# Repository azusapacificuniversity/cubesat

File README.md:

# cubesat
This repository houses the design documents, files, code, etc in a multi-year project for [Azusa Pacific Univeristy](https://www.apu.edu/)'s department of [Engineering and Computer Science](https://www.apu.edu/clas/computerscience/) to design, fabricate, test, and have launched our very own nanosatellite!

A great primer on CubeSats is [NASA's CubeSat 101: Basic Concepts and Processes for First-Time CubeSat Developers (pdf)](https://www.nasa.gov/sites/default/files/atoms/files/nasa_csli_cubesat_101_508.pdf) from their page [https://www.nasa.gov/content/cubesat-launch-initiative-resources](https://www.nasa.gov/content/cubesat-launch-initiative-resources).

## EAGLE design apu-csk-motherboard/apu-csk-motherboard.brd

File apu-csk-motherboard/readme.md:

[Autodesk Eagle](https://www.autodesk.com/products/eagle/) Schematic, Board, and Library files for an APU-designed Open Source Hardware Pumpkin CubeSat
Kit-compatible Slot 0 Motherboard.  

This is a template, mechanically it should work, but electrically it doesn't really do much yet.  This is the
board outline and connectors for the main modules: a 104-pin CSK bus
with H1 and H2 connectors, an [iceWerx module](https://www.robotshop.com/en/devantech-icewerx-ice40-hx8k-fpga.html) with a Lattice iCE40HX8K
FPGA, and a Feather-compatible socket, which can take any number of
microcontroller boards such as the [SparkFun RISC-V RED-V Thing Plus](https://www.sparkfun.com/products/15799) or the
[Adafruit ESP32 Feather](https://www.adafruit.com/product/3405).  

This board is designed to work with the [Pumpkin Space](https://www.pumpkinspace.com/) - [CubeSat Kit Frame](http://cubesatkit.com/), for example parts:
```
710-00794       Base Plate Assembly
703-00289       Chassis Walls
710-00713       Large Aperture Cover Plate Assembly
```
from https://www.pumpkinspace.com/

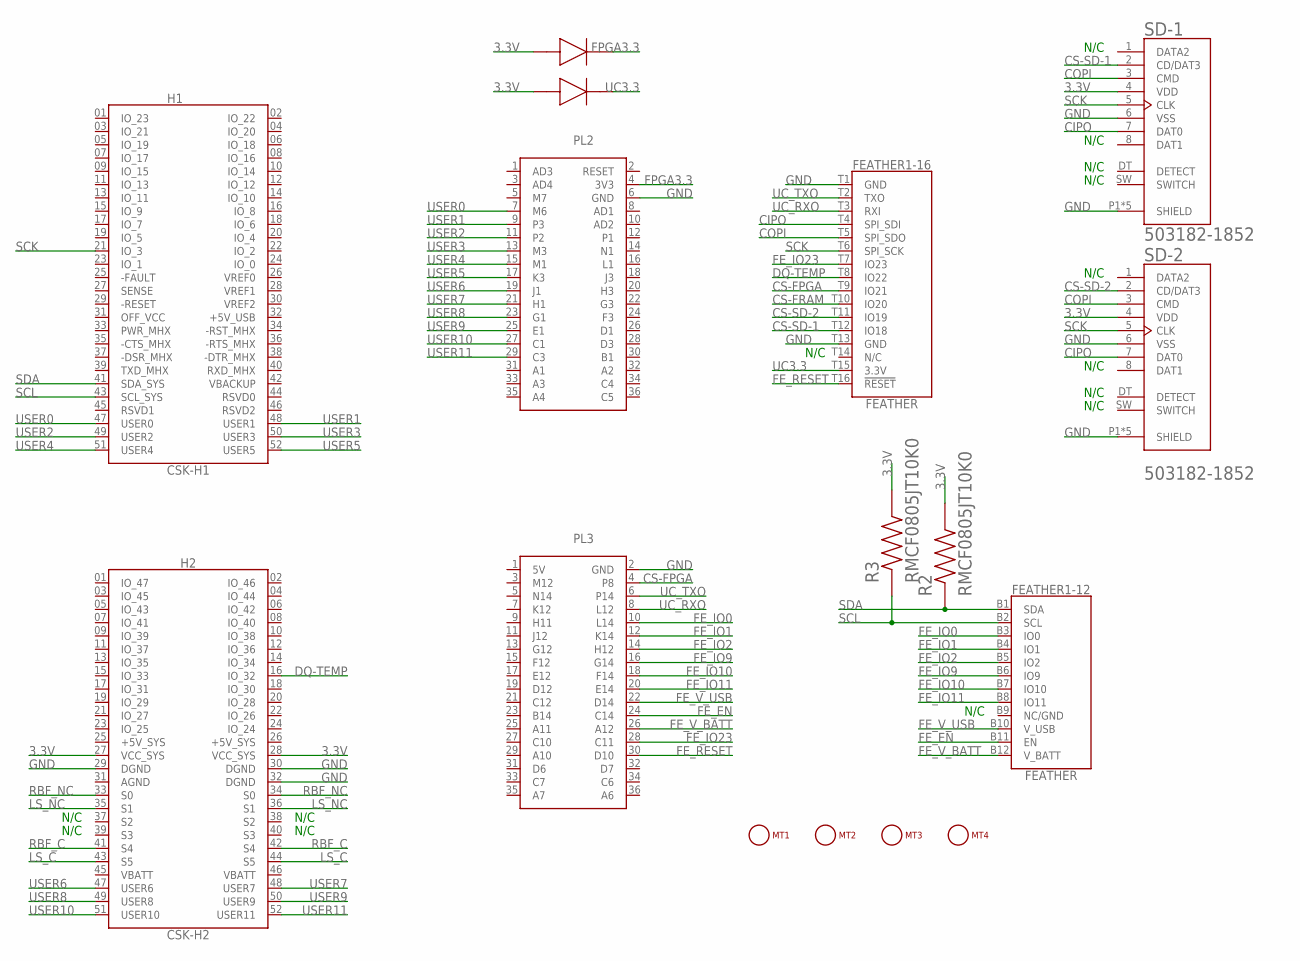
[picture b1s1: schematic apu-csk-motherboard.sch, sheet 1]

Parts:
B1, B2: DIO_PMEG4030ER,115
FEATHER1: FEATHER
H1: CSK-H1; SAMTEC_ESQ-126-37-G-D--NUMBERED-FOR-CUBESAT-BUS
H2: CSK-H2; SAMTEC_ESQ-126-37-G-D--NUMBERED-FOR-CUBESAT-BUS
MT1, MT2, MT3, MT4: MOUNTING_HOLE-125_250_ROUND; MT_125_250
PL2: ICEWERX-PL2; TE_4-1734506-1
PL3: ICEWERX-PL3; TE_4-1734506-1
R2, R3: RMCF0805JT10K0; RESC2012X65N
SD-1, SD-2: 503182-1852; MOLEX_503182-1852

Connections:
3.3V: B1.2 (ANODE), B2.2 (ANODE), H2.27 (VCC_SYS), H2.28 (VCC_SYS), R2.2, R3.2, SD-1.4 (VDD), SD-2.4 (VDD); also elsewhere on the board
CIPO: FEATHER1.T4 (SPI_SDI), SD-1.7 (DAT0), SD-2.7 (DAT0); also elsewhere on the board
COPI: FEATHER1.T5 (SPI_SDO), SD-1.3 (CMD), SD-2.3 (CMD); also elsewhere on the board
CS-FPGA: FEATHER1.T9 (IO21), PL3.4 (P8)
CS-FRAM: FEATHER1.T10 (IO20); also elsewhere on the board
CS-SD-1: FEATHER1.T12 (IO18), SD-1.2 (CD/DAT3)
CS-SD-2: FEATHER1.T11 (IO19), SD-2.2 (CD/DAT3)
DQ-TEMP: FEATHER1.T8 (IO22), H2.16 (IO_32); also elsewhere on the board
FE_EN: FEATHER1.B11 (EN), PL3.24 (C14)
FE_IO0: FEATHER1.B3 (IO0), PL3.10 (L14)
FE_IO1: FEATHER1.B4 (IO1), PL3.12 (K14)
FE_IO2: FEATHER1.B5 (IO2), PL3.14 (H12)
FE_IO9: FEATHER1.B6 (IO9), PL3.16 (G14)
FE_IO10: FEATHER1.B7 (IO10), PL3.18 (F14)
FE_IO11: FEATHER1.B8 (IO11), PL3.20 (E14)
FE_IO23: FEATHER1.T7 (IO23), PL3.28 (C11)
FE_RESET: FEATHER1.T16 (!RESET), PL3.30 (D10)
FE_V_BATT: FEATHER1.B12 (V_BATT), PL3.26 (A12)
FE_V_USB: FEATHER1.B10 (V_USB), PL3.22 (D14)
FPGA3.3: B1.1 (CATHODE), PL2.4 (3V3)
GND: FEATHER1.T1 (GND), FEATHER1.T13 (GND), H2.29 (DGND), H2.30 (DGND), H2.32 (DGND), PL2.6 (GND), PL3.2 (GND), SD-1.6 (VSS), SD-1.P1 (SHIELD), SD-1.P2 (SHIELD), SD-1.P3 (SHIELD), SD-1.P4 (SHIELD), SD-1.P5 (SHIELD), SD-2.6 (VSS), SD-2.P1 (SHIELD), SD-2.P2 (SHIELD), SD-2.P3 (SHIELD), SD-2.P4 (SHIELD), SD-2.P5 (SHIELD); also elsewhere on the board
LS_C: H2.43 (S5), H2.44 (S5); also elsewhere on the board
LS_NC: H2.35 (S1), H2.36 (S1); also elsewhere on the board
RBF_C: H2.41 (S4), H2.42 (S4); also elsewhere on the board
RBF_NC: H2.33 (S0), H2.34 (S0); also elsewhere on the board
SCK: FEATHER1.T6 (SPI_SCK), H1.21 (IO_3), SD-1.5 (CLK), SD-2.5 (CLK); also elsewhere on the board
SCL: FEATHER1.B2 (SCL), H1.43 (SCL_SYS), R3.1; also elsewhere on the board
SDA: FEATHER1.B1 (SDA), H1.41 (SDA_SYS), R2.1; also elsewhere on the board
UC3.3: B2.1 (CATHODE), FEATHER1.T15 (3.3V)
UC_RXO: FEATHER1.T3 (RXI), PL3.8 (L12)
UC_TXO: FEATHER1.T2 (TXO), PL3.6 (P14)
USER0: H1.47 (USER0), PL2.7 (M6)
USER1: H1.48 (USER1), PL2.9 (P3)
USER2: H1.49 (USER2), PL2.11 (P2)
USER3: H1.50 (USER3), PL2.13 (M3)
USER4: H1.51 (USER4), PL2.15 (M1)
USER5: H1.52 (USER5), PL2.17 (K3)
USER6: H2.47 (USER6), PL2.19 (J1)
USER7: H2.48 (USER7), PL2.21 (H1)
USER8: H2.49 (USER8), PL2.23 (G1)
USER9: H2.50 (USER9), PL2.25 (E1)
USER10: H2.51 (USER10), PL2.27 (C1)
USER11: H2.52 (USER11), PL2.29 (C3)

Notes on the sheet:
N/C

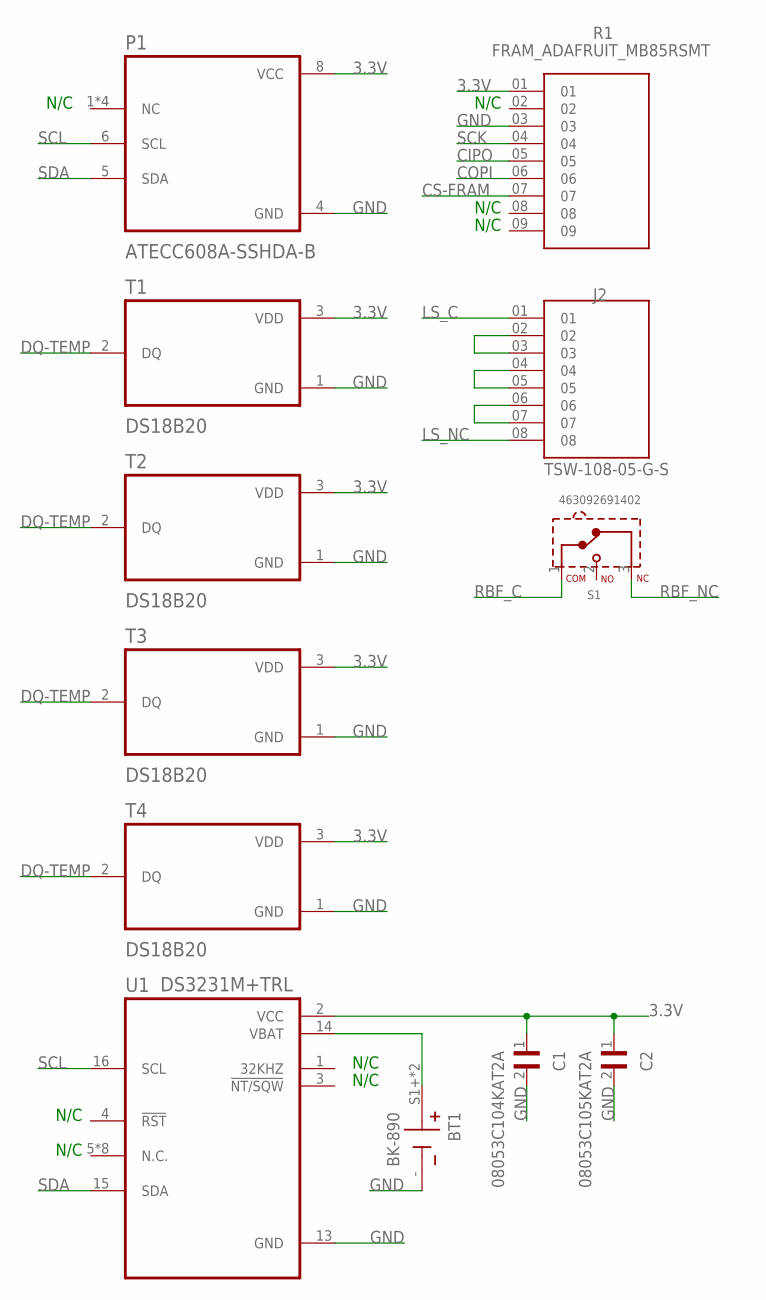
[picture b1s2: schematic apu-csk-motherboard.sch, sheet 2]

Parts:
BT1: BK-890; BAT_BK-890
C1: 08053C104KAT2A; CAPC2012X94N
C2: 08053C105KAT2A; CAPC2012X94N
J2: TSW-108-05-G-S; SAMTEC_TSW-108-05-G-S
P1: ATECC608A-SSHDA-B; SOIC127P600X175-8N
R1: FRAM_ADAFRUIT_MB85RSMT
S1: 463092691402
T1, T2, T3, T4: DS18B20; TO92269P495H695-3
U1: DS3231M+TRL; SOIC127P1032X265-16N

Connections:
3.3V: C1.1, C2.1, P1.8 (VCC), R1.01, T1.3 (VDD), T2.3 (VDD), T3.3 (VDD), T4.3 (VDD), U1.2 (VCC); also elsewhere on the board
CIPO: R1.05; also elsewhere on the board
COPI: R1.06; also elsewhere on the board
CS-FRAM: R1.07; also elsewhere on the board
DQ-TEMP: T1.2 (DQ), T2.2 (DQ), T3.2 (DQ), T4.2 (DQ); also elsewhere on the board
GND: BT1.-, C1.2, C2.2, P1.4 (GND), R1.03, T1.1 (GND), T2.1 (GND), T3.1 (GND), T4.1 (GND), U1.13 (GND); also elsewhere on the board
LS_C: J2.01; also elsewhere on the board
LS_NC: J2.08; also elsewhere on the board
unnamed: BT1.S1+ (+), BT1.S2+ (+), U1.14 (VBAT)
unnamed: J2.02, J2.03
unnamed: J2.04, J2.05
unnamed: J2.06, J2.07
RBF_C: S1.1 (COM); also elsewhere on the board
RBF_NC: S1.3 (NC); also elsewhere on the board
SCK: R1.04; also elsewhere on the board
SCL: P1.6 (SCL), U1.16 (SCL); also elsewhere on the board
SDA: P1.5 (SDA), U1.15 (SDA); also elsewhere on the board

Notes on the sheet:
N/C

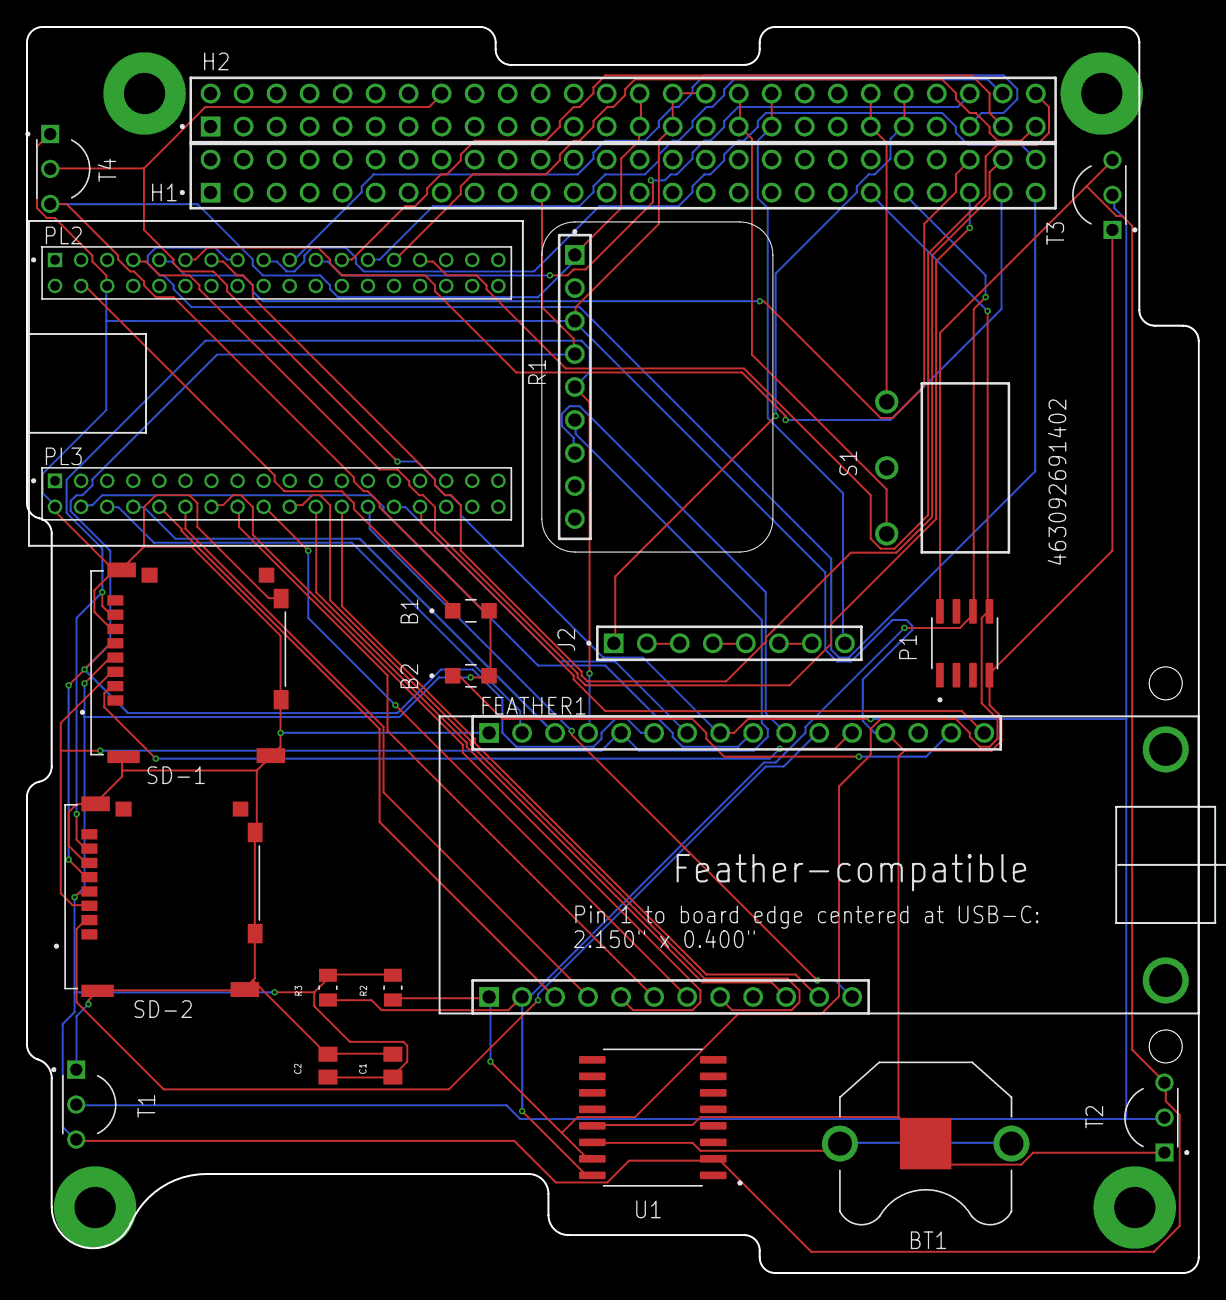
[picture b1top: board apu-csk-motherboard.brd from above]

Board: 2 copper layers, 90.2 x 95.9 mm, 27 parts (0 on the bottom side), 47 nets.

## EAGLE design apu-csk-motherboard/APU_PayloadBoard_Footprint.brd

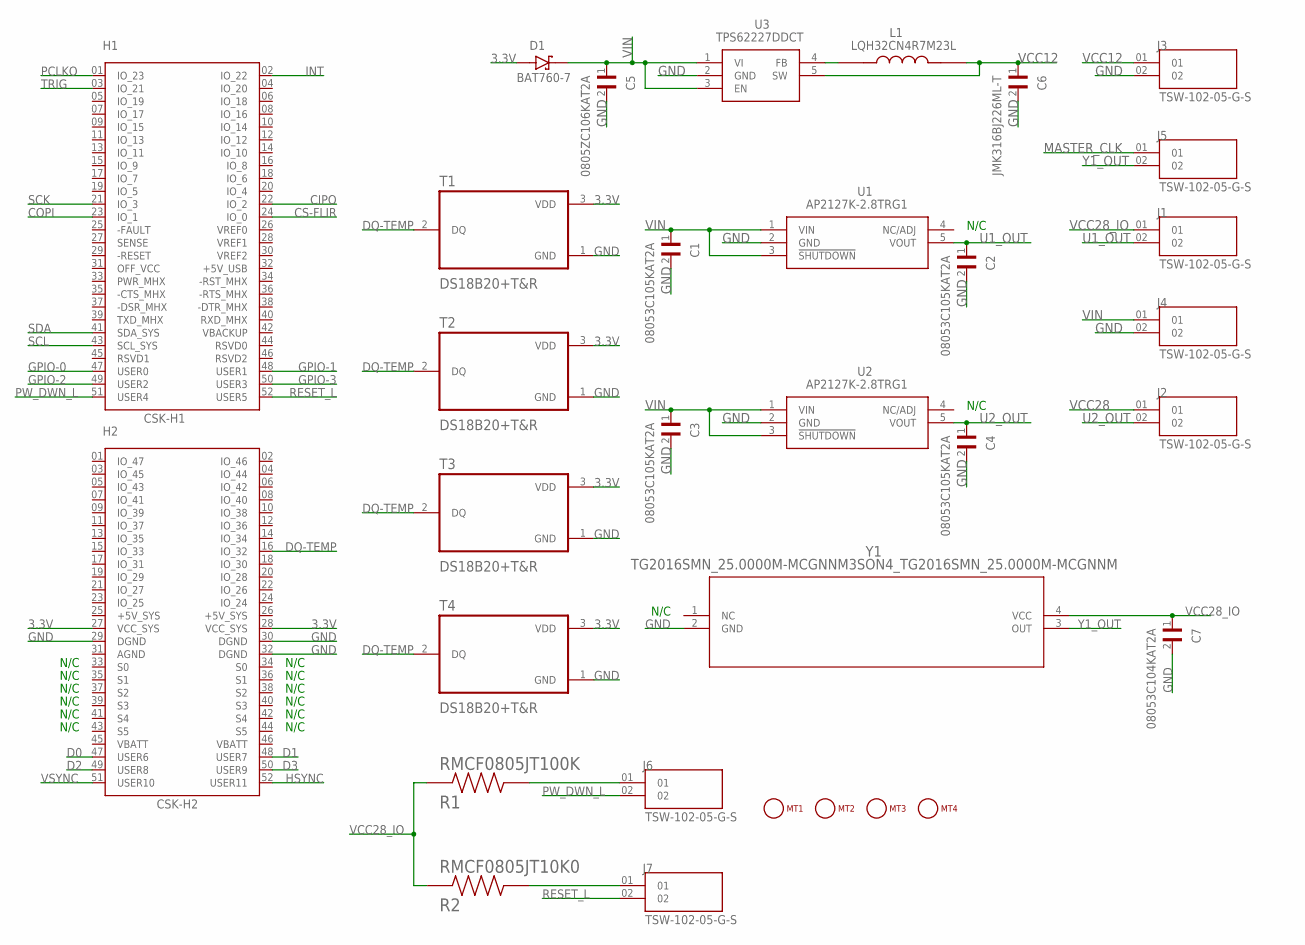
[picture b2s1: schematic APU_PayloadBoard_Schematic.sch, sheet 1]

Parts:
C1, C2, C3, C4: 08053C105KAT2A; CAPC2012X94N
C5: 0805ZC106KAT2A; CAPC2012X152N
C6: JMK316BJ226ML-T; CAPC3216X180N
C7: 08053C104KAT2A; CAPC2012X94N
D1: BAT760-7; SOD2513X120N
H1: CSK-H1; SAMTEC_ESQ-126-37-G-D--NUMBERED-FOR-CUBESAT-BUS
H2: CSK-H2; SAMTEC_ESQ-126-37-G-D--NUMBERED-FOR-CUBESAT-BUS
J1, J2, J3, J4, J5, J6, J7: TSW-102-05-G-S; SAMTEC_TSW-102-05-G-S
L1: LQH32CN4R7M23L; IND_LQH32CN4R7M23L
MT1, MT2, MT3, MT4: MOUNTING_HOLE-125_250_ROUND; MT_125_250
R1: RMCF0805JT100K; RESC2012X65N
R2: RMCF0805JT10K0; RESC2012X65N
T1, T2, T3, T4: DS18B20+T&R
U1, U2: AP2127K-2.8TRG1; SOT95P282X145-5N
U3: TPS62227DDCT; SOT95P280X110-5N
Y1: TG2016SMN_25.0000M-MCGNNM3SON4_TG2016SMN_25.0000M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; SON4_TG2016SMN_25.0000M-MCGNNM

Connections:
3.3V: D1.A, H2.27 (VCC_SYS), H2.28 (VCC_SYS), T1.3 (VDD), T2.3 (VDD), T3.3 (VDD), T4.3 (VDD); also elsewhere on the board
CIPO: H1.22 (IO_2); also elsewhere on the board
COPI: H1.23 (IO_1); also elsewhere on the board
CS-FLIR: H1.24 (IO_0); also elsewhere on the board
D0: H2.47 (USER6); also elsewhere on the board
D1: H2.48 (USER7); also elsewhere on the board
D2: H2.49 (USER8); also elsewhere on the board
D3: H2.50 (USER9); also elsewhere on the board
DQ-TEMP: H2.16 (IO_32), T1.2 (DQ), T2.2 (DQ), T3.2 (DQ), T4.2 (DQ)
GND: C1.2, C2.2, C3.2, C4.2, C5.2, C6.2, C7.2, H2.29 (DGND), H2.30 (DGND), H2.32 (DGND), J3.02, J4.02, T1.1 (GND), T2.1 (GND), T3.1 (GND), T4.1 (GND), U1.2 (GND), U2.2 (GND), U3.2 (GND), Y1.2 (GND); also elsewhere on the board
GPIO-0: H1.47 (USER0); also elsewhere on the board
GPIO-1: H1.48 (USER1); also elsewhere on the board
GPIO-2: H1.49 (USER2); also elsewhere on the board
GPIO-3: H1.50 (USER3); also elsewhere on the board
HSYNC: H2.52 (USER11); also elsewhere on the board
INT: H1.02 (IO_22); also elsewhere on the board
MASTER_CLK: J5.01; also elsewhere on the board
unnamed: L1.1, U3.4 (FB)
unnamed: J6.01, R1.2
unnamed: J7.01, R2.2
PCLKO: H1.01 (IO_23); also elsewhere on the board
PW_DWN_L: H1.51 (USER4), J6.02; also elsewhere on the board
RESET_L: H1.52 (USER5), J7.02; also elsewhere on the board
SCK: H1.21 (IO_3); also elsewhere on the board
SCL: H1.43 (SCL_SYS); also elsewhere on the board
SDA: H1.41 (SDA_SYS); also elsewhere on the board
TRIG: H1.03 (IO_21); also elsewhere on the board
U1_OUT: C2.1, J1.02, U1.5 (VOUT)
U2_OUT: C4.1, J2.02, U2.5 (VOUT)
VCC12: C6.1, J3.01, L1.2, U3.5 (SW); also elsewhere on the board
VCC28: J2.01; also elsewhere on the board
VCC28_IO: C7.1, J1.01, R1.1, R2.1, Y1.4 (VCC); also elsewhere on the board
VIN: C1.1, C3.1, C5.1, D1.C (K), J4.01, U1.1 (VIN), U1.3 (!SHUTDOWN), U2.1 (VIN), U2.3 (!SHUTDOWN), U3.1 (VI), U3.3 (EN)
VSYNC: H2.51 (USER10); also elsewhere on the board
Y1_OUT: J5.02, Y1.3 (OUT)

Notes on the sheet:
N/C

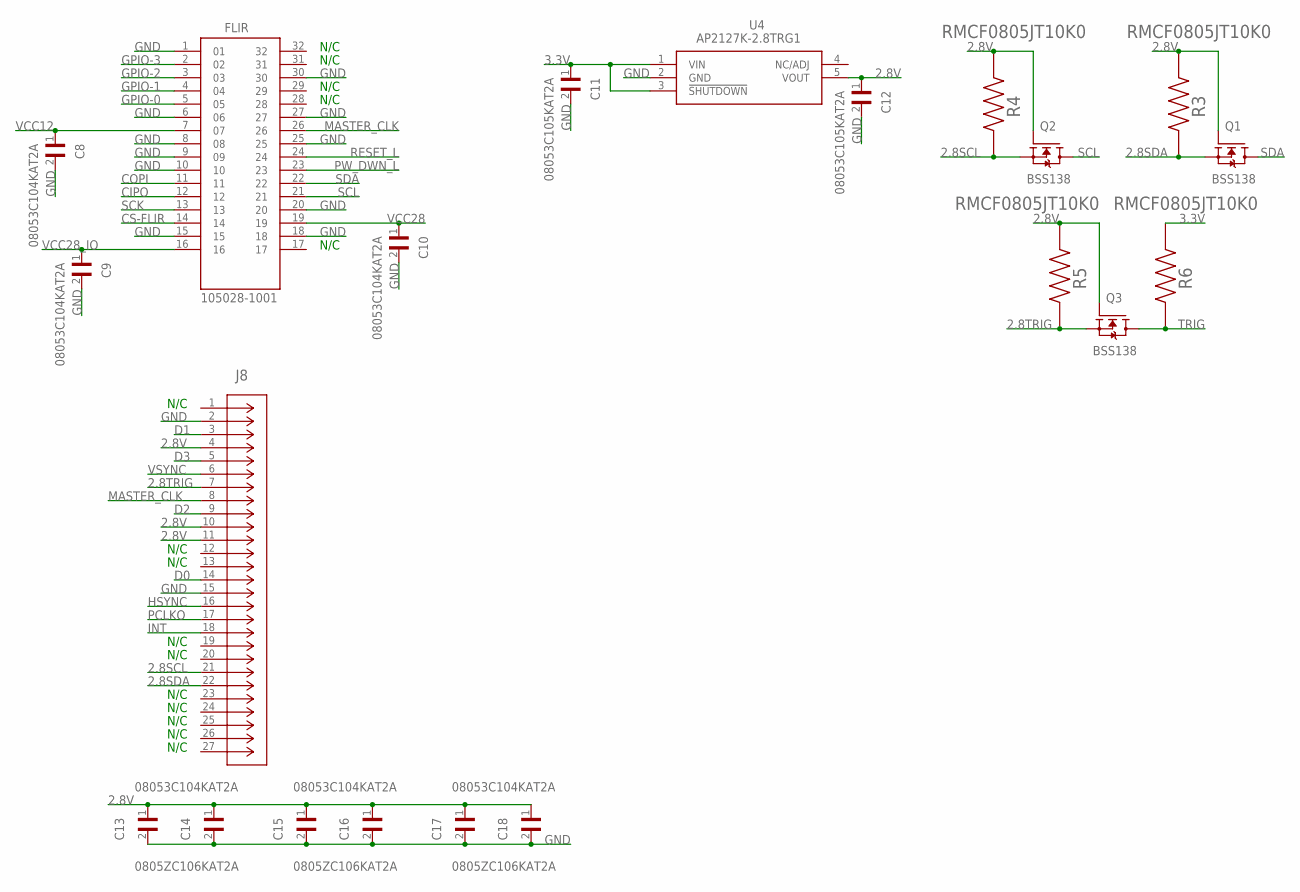
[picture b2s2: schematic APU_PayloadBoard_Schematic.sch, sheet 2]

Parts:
C8, C9, C10, C13, C15, C17: 08053C104KAT2A; CAPC2012X94N
C11, C12: 08053C105KAT2A; CAPC2012X94N
C14, C16, C18: 0805ZC106KAT2A; CAPC2012X152N
FLIR: 105028-1001; MOLEX_105028-1001
J8: SFV25R-1STE1LFCON25_1X25_DR_SFV_JAE; CON25_1X25_DR_SFV_JAE
Q1, Q2, Q3: BSS138; SOT95P240X111-3N
R3, R4, R5, R6: RMCF0805JT10K0; RESC2012X65N
U4: AP2127K-2.8TRG1; SOT95P282X145-5N

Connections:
2.8SCL: J8.21, Q2.2 (S), R4.1
2.8SDA: J8.22, Q1.2 (S), R3.1
2.8TRIG: J8.7, Q3.2 (S), R5.1
2.8V: C12.1, C13.1, C14.1, C15.1, C16.1, C17.1, C18.1, J8.4, J8.10, J8.11, Q1.1 (G), Q2.1 (G), Q3.1 (G), R3.2, R4.2, R5.2, U4.5 (VOUT)
3.3V: C11.1, R6.2, U4.1 (VIN), U4.3 (!SHUTDOWN); also elsewhere on the board
CIPO: FLIR.12; also elsewhere on the board
COPI: FLIR.11; also elsewhere on the board
CS-FLIR: FLIR.14; also elsewhere on the board
D0: J8.14; also elsewhere on the board
D1: J8.3; also elsewhere on the board
D2: J8.9; also elsewhere on the board
D3: J8.5; also elsewhere on the board
GND: C8.2, C9.2, C10.2, C11.2, C12.2, C13.2, C14.2, C15.2, C16.2, C17.2, C18.2, FLIR.1, FLIR.6, FLIR.8, FLIR.9, FLIR.10, FLIR.15, FLIR.18, FLIR.20, FLIR.25, FLIR.27, FLIR.30, J8.2, J8.15, U4.2 (GND); also elsewhere on the board
GPIO-0: FLIR.5; also elsewhere on the board
GPIO-1: FLIR.4; also elsewhere on the board
GPIO-2: FLIR.3; also elsewhere on the board
GPIO-3: FLIR.2; also elsewhere on the board
HSYNC: J8.16; also elsewhere on the board
INT: J8.18; also elsewhere on the board
MASTER_CLK: FLIR.26, J8.8; also elsewhere on the board
PCLKO: J8.17; also elsewhere on the board
PW_DWN_L: FLIR.23; also elsewhere on the board
RESET_L: FLIR.24; also elsewhere on the board
SCK: FLIR.13; also elsewhere on the board
SCL: FLIR.21, Q2.3 (D); also elsewhere on the board
SDA: FLIR.22, Q1.3 (D); also elsewhere on the board
TRIG: Q3.3 (D), R6.1; also elsewhere on the board
VCC12: C8.1, FLIR.7; also elsewhere on the board
VCC28: C10.1, FLIR.19; also elsewhere on the board
VCC28_IO: C9.1, FLIR.16; also elsewhere on the board
VSYNC: J8.6; also elsewhere on the board

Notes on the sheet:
N/C

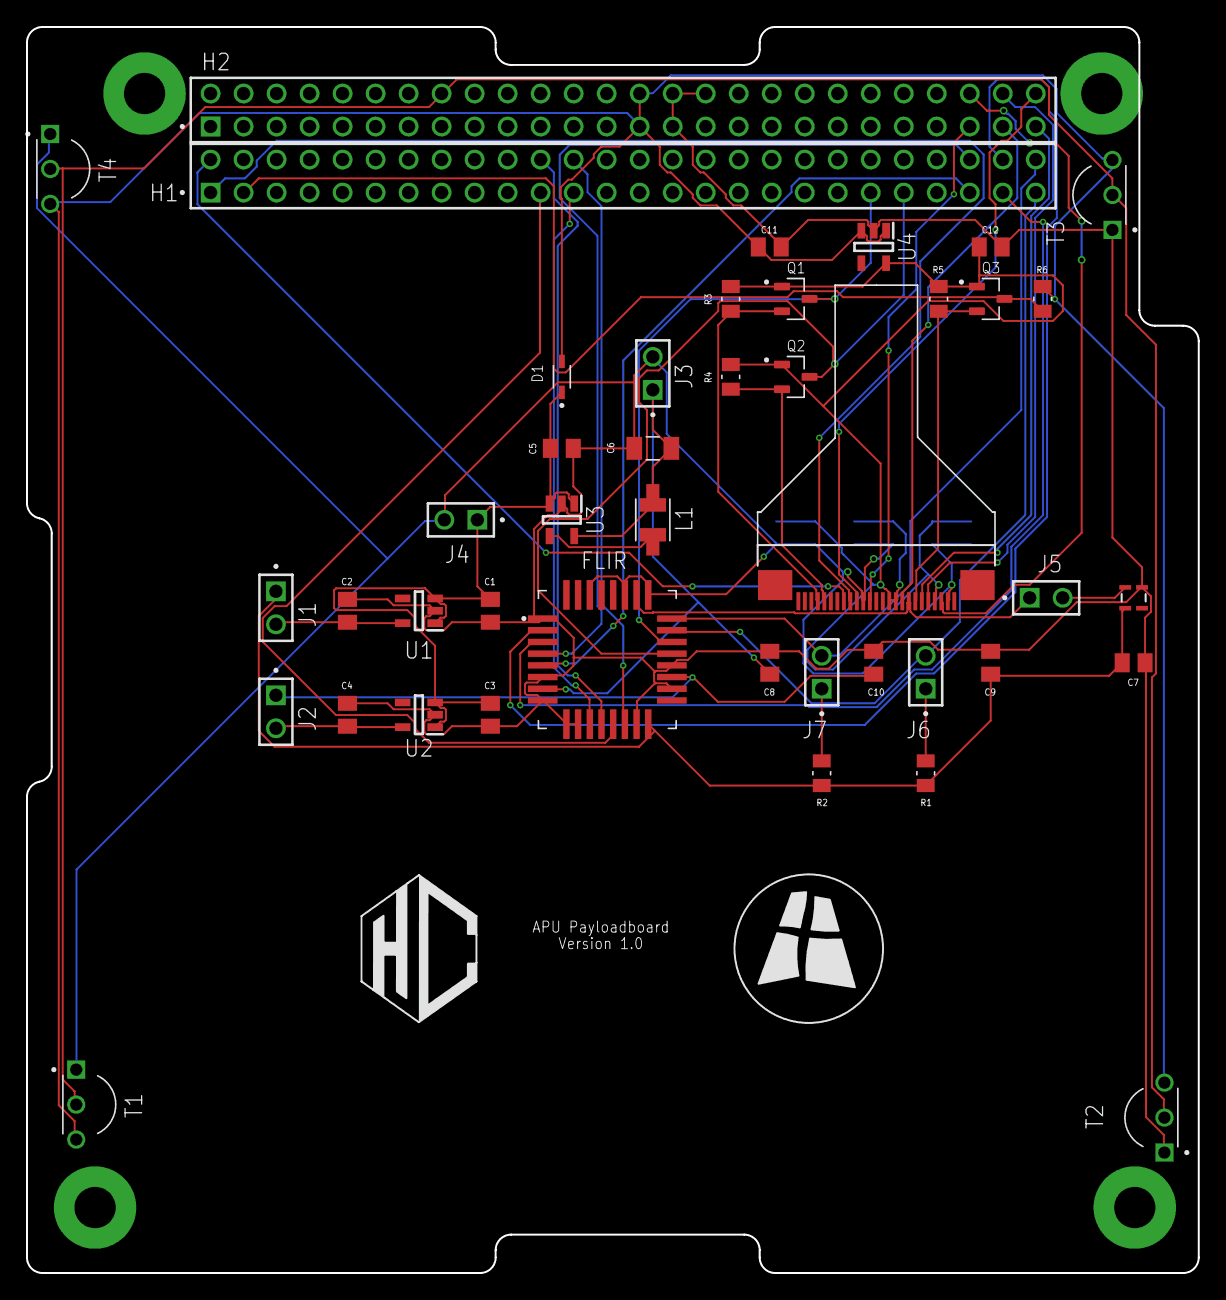
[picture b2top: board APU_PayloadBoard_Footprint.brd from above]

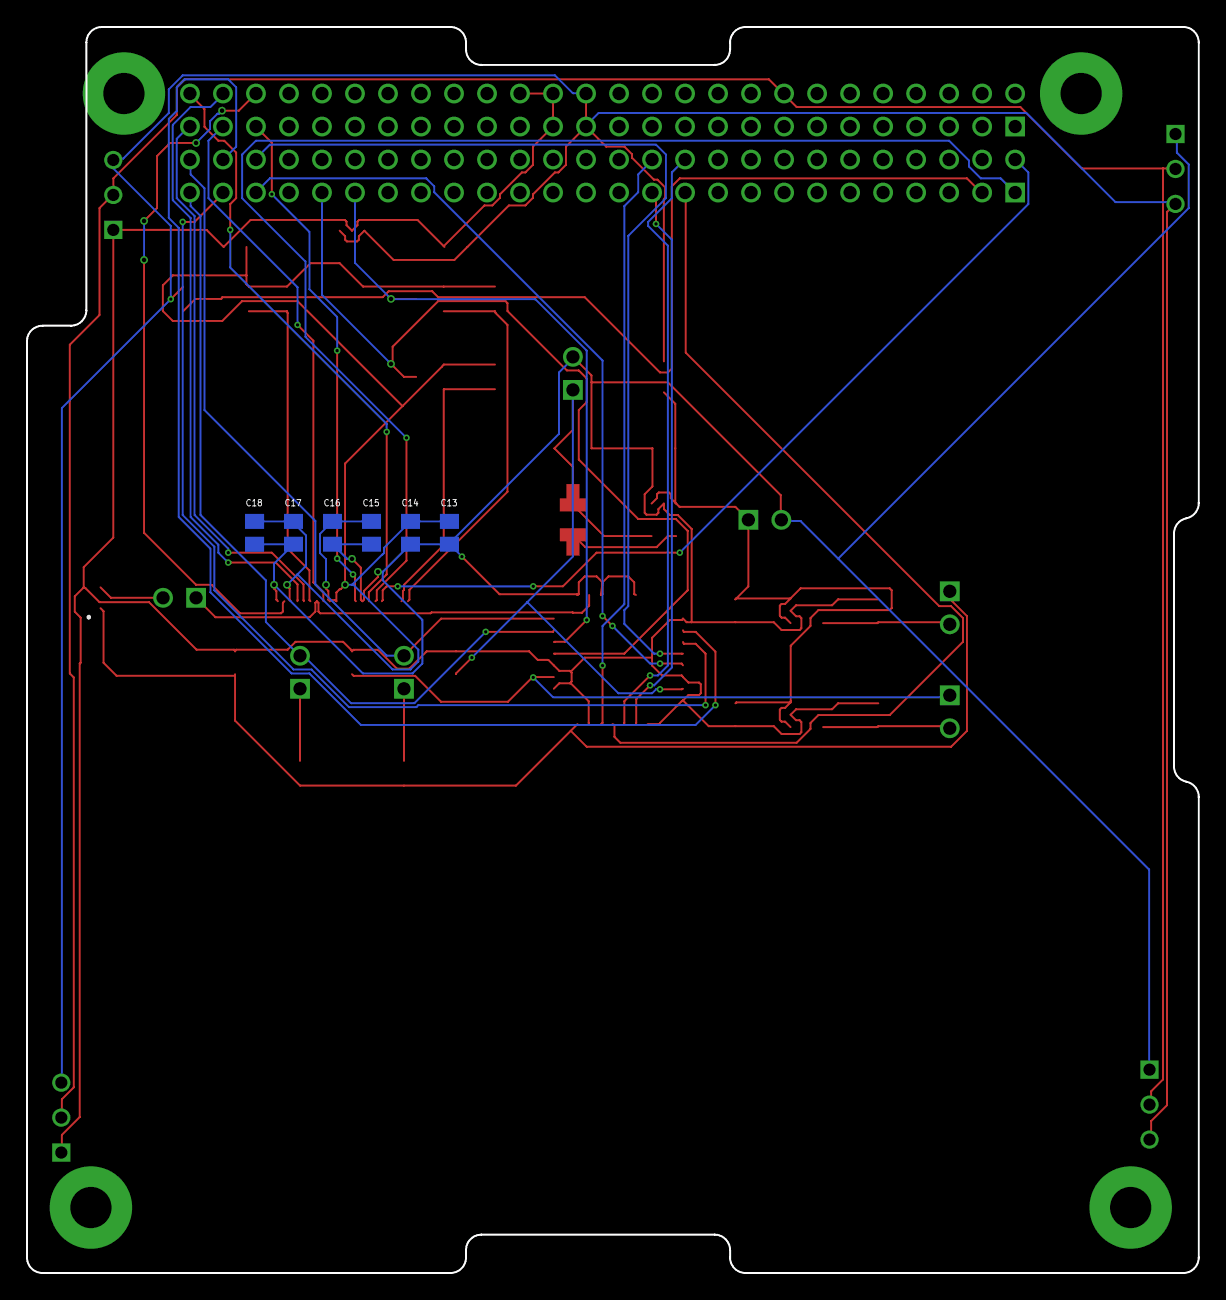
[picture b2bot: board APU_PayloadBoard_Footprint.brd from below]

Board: 2 copper layers, 90.2 x 95.9 mm, 55 parts (6 on the bottom side), 39 nets.

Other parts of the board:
U$1: APU-LOGO
U$2: NATHANAEL-LOGO

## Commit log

2020-04-14 Update README.md
    Added links to APU, ECS and NASA's CubeSat 101 document.
2022-11-12 Add initial motherboard eagle files
    Initial Eagle Schematic, Board, and Library files for a Pumpkin CubeSat
    Kit-compatible Slot 0 Motherboard. This is a template, mechanically it
    should work, but electrically it doesn't really do much yet. This is the
    board outline and connectors for the main modules: a 104-pin CSK bus
    with H1 and H2 connectors, an iceWerx module with a Lattice iCE40HX8K
    FPGA, and a Feather-compatible socket, which can take any number of
2022-11-12 Move to folder, add pdf of board and schematic
2022-11-12 add readme file describing this board
2022-11-17 Create apu-csk-motherboard.b##
2023-01-08 added the sd card schematic to the library
2023-01-08 Started Connecting the SD Card to the MicroController
2023-01-23 Proper SD Card
2023-01-24 Corrected the Detect and Swith on the SD Card
2023-02-21 Added 4 temperature sensors, Authenitcation Chip, and Conncetors for RBF Switch
2023-02-23 Added the components to a second sheet and finished wiring the authenticator chip
2023-03-22 Added FRAM and RTC but need to finish connections
2023-04-14 Add files via upload
    This demonstrated the fact that APU ECS is a part of the AMSAT leaderboard where we reported collects from their satellites.
2023-04-14 Add files via upload
    ENGR480 Capstone Presentation that highlighted our initial deployment of our CubeSat ground station
2023-04-18 Just need to add capacitors
2023-04-21 Prototype Board for revision
2023-04-24 JR and Nathanael Review
2023-05-15 Almost done
2023-05-19 JR to review
2023-05-20 RBF Placement
2023-07-04 Add files via upload
    These files are in Fusion360 and after they get checked I will add all necessary files :)
2023-07-19 Add files via upload
    Prototype-Mark_1-Finalized

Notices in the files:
parts and their libraries:
COPYRIGHT: Copyright (C) 2023 Ultra Librarian. All rights reserved.
